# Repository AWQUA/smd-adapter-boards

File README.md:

# smd-adapter-boards

###This is a collection of adapter circuit boards that make it easier to incorporate [Surface Mount Device (SMD)](https://en.wikipedia.org/wiki/Surface-mount_technology) into breadboard prototypes. 

#####Please note that individual SMD components may not exactly fit our SMD footprints -- manufacturers do not always design their components to adhere strictly to stated footprints. Check the descriptions of particular adapter boards below for SMD components that we have verified to fit a given board.

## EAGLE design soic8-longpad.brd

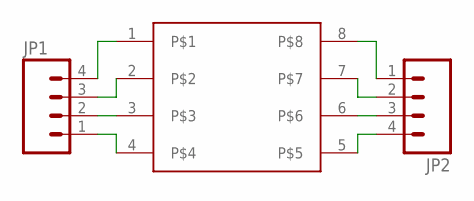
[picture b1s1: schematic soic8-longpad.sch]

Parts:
JP1, JP2: M04NO_SILK_ALL_ROUND; 1X04_NO_SILK_ALL_ROUND
U$1: SOIC8; SOIC8-LONGPAD

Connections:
unnamed: JP1.4, U$1.1
unnamed: JP1.3, U$1.2
unnamed: JP1.2, U$1.3
unnamed: JP1.1, U$1.4
unnamed: JP2.1, U$1.8
unnamed: JP2.2, U$1.7
unnamed: JP2.3, U$1.6
unnamed: JP2.4, U$1.5

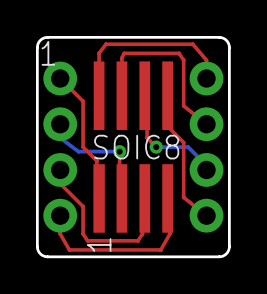
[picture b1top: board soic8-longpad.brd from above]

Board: 2 copper layers, 10.7 x 12.2 mm, 3 parts (0 on the bottom side), 8 nets.

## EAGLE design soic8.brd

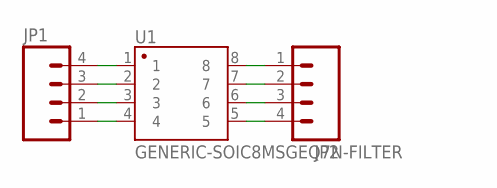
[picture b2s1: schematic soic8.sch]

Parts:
JP1, JP2: M04NO_SILK_ALL_ROUND; 1X04_NO_SILK_ALL_ROUND
U1: GENERIC-SOIC8MSGEQ7N-FILTER; SO08

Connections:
unnamed: JP1.3, U1.2
unnamed: JP1.1, U1.4
unnamed: JP1.2, U1.3
unnamed: JP2.1, U1.8
unnamed: JP2.2, U1.7
unnamed: JP2.3, U1.6
unnamed: JP2.4, U1.5
unnamed: JP1.4, U1.1

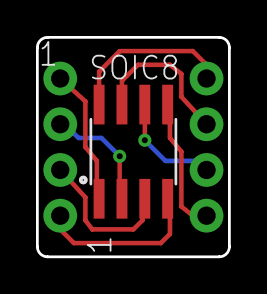
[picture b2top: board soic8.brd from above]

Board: 2 copper layers, 10.7 x 12.2 mm, 3 parts (0 on the bottom side), 8 nets.

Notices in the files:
parts and their libraries:
SparkFun-Connectors: Licensing: Creative Commons ShareAlike 4.0 International - https://creativecommons.org/licenses/by-sa/4.0
